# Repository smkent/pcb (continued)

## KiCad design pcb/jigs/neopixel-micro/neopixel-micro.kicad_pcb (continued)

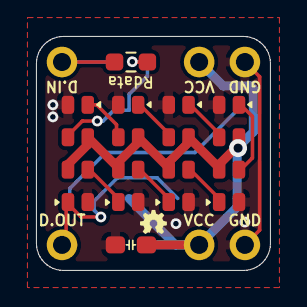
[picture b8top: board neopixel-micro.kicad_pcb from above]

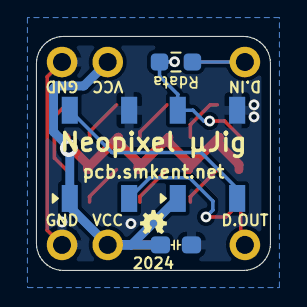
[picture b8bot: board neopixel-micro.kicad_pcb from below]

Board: 2 copper layers, 13.0 x 13.0 mm, 18 parts (8 on the bottom side), 13 nets.
